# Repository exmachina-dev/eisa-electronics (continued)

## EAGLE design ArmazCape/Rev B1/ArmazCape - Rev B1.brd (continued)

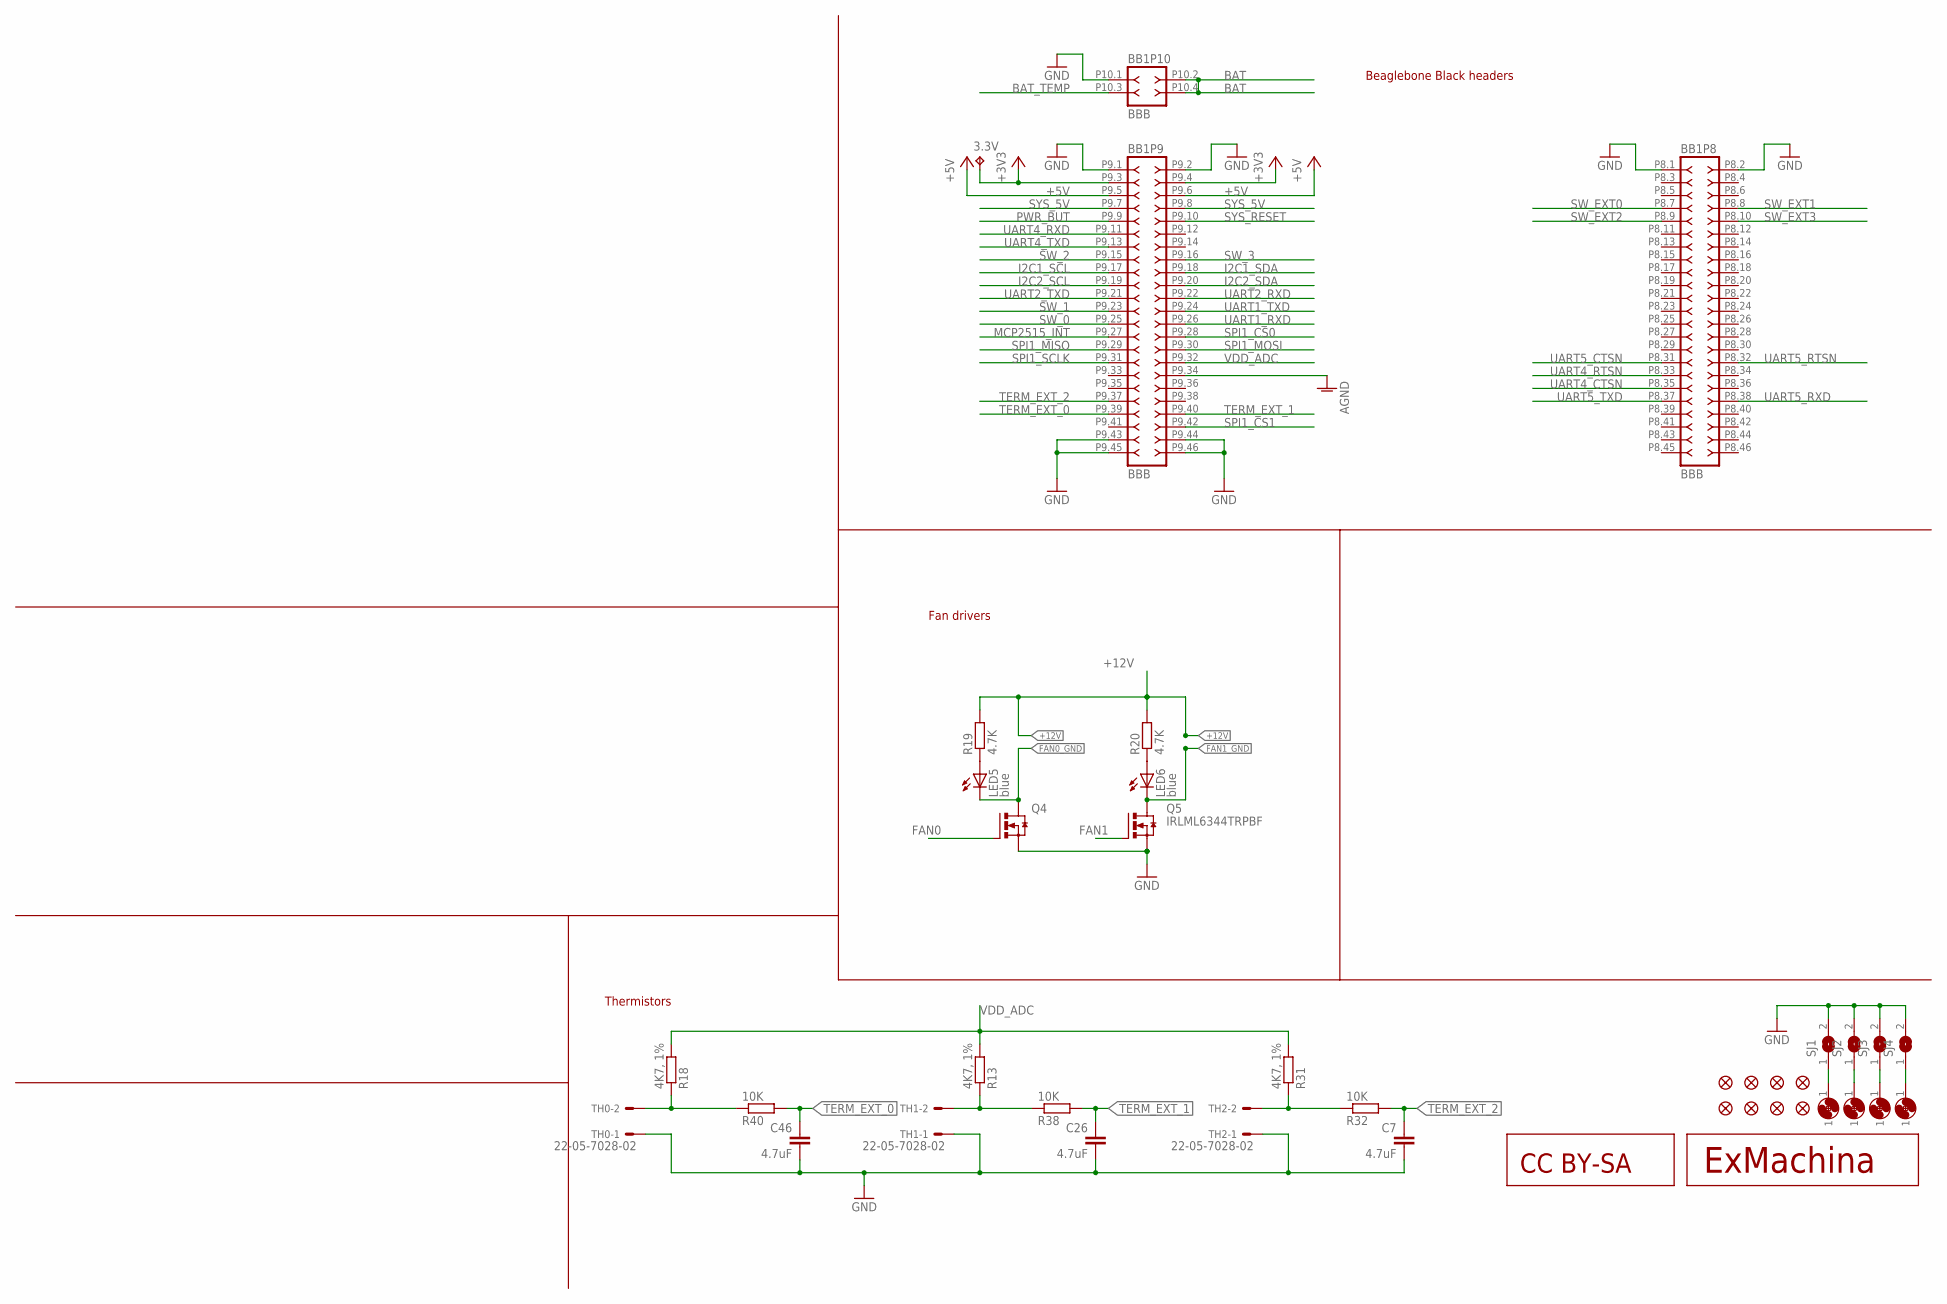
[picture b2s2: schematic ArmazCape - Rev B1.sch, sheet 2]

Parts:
3.3V: TPB1,27; B1,27
BB1: BBB
C7, C26, C46: 4.7uF; C0603; MPN MC0603X475K6R3CT
FI1, FI2, FI3, FI4, FI5, FI6, FI7, FI8: FIDUCIAL1X2; FIDUCIAL-1X2
H1, H2, H3, H4: MOUNT-PAD3,0; P3,0
LED5, LED6: blue; CHIP-LED0603; MPN OVS-0603
Q4, Q5: IRLML6344TRPBF; SOT95P240X112-3N
R13, R18, R31: 4K7, 1%; R0603; MPN MCMR06X4701FTL
R19, R20: 4.7K; R0603; MPN MCMR06X4701FTL
R32, R38, R40: 10K; R0603; MPN MCMR06X1002FTL
SJ1, SJ2, SJ3, SJ4: SJ
TH0, TH1, TH2: 22-05-7028-02; 7395-02; MPN 22-05-7028
U$1: EXMACHINA-LOGO-NAME; EXM-LOGO-BASELINE
U$2: CC-BY-SA

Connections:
+3V3: 3.3V.TP, BB1.P9.3 (3), BB1.P9.4 (4); also elsewhere on the board
+5V: BB1.P9.5 (5), BB1.P9.6 (6); also elsewhere on the board
+12V: R19.2, R20.2; also elsewhere on the board
AGND: BB1.P9.34 (34)
BAT: BB1.P10.2 (2), BB1.P10.4 (4); also elsewhere on the board
BAT_TEMP: BB1.P10.3 (3); also elsewhere on the board
FAN0: Q4.1 (G); also elsewhere on the board
FAN0_GND: LED5.C, Q4.3 (D); also elsewhere on the board
FAN1: Q5.1 (G); also elsewhere on the board
FAN1_GND: LED6.C, Q5.3 (D); also elsewhere on the board
GND: BB1.P8.1 (1), BB1.P8.2 (2), BB1.P9.1 (1), BB1.P9.2 (2), BB1.P9.43 (43), BB1.P9.44 (44), BB1.P9.45 (45), BB1.P9.46 (46), BB1.P10.1 (1), C7.2, C26.2, C46.2, Q4.2 (S), Q5.2 (S), SJ1.2, SJ2.2, SJ3.2, SJ4.2, TH0.1, TH1.1, TH2.1; also elsewhere on the board
I2C1_SCL: BB1.P9.17 (17)
I2C1_SDA: BB1.P9.18 (18)
I2C2_SCL: BB1.P9.19 (19); also elsewhere on the board
I2C2_SDA: BB1.P9.20 (20); also elsewhere on the board
MCP2515_INT: BB1.P9.27 (27); also elsewhere on the board
unnamed: LED5.A, R19.1
unnamed: R31.1, R32.1, TH2.2
unnamed: H4.1, SJ1.1
unnamed: H3.1, SJ2.1
unnamed: H2.1, SJ3.1
unnamed: H1.1, SJ4.1
unnamed: LED6.A, R20.1
unnamed: R13.1, R38.1, TH1.2
unnamed: R18.1, R40.1, TH0.2
PWR_BUT: BB1.P9.9 (9)
SPI1_CS0: BB1.P9.28 (28); also elsewhere on the board
SPI1_CS1: BB1.P9.42 (42)
SPI1_MISO: BB1.P9.29 (29); also elsewhere on the board
SPI1_MOSI: BB1.P9.30 (30); also elsewhere on the board
SPI1_SCLK: BB1.P9.31 (31); also elsewhere on the board
SW_0: BB1.P9.25 (25); also elsewhere on the board
SW_1: BB1.P9.23 (23); also elsewhere on the board
SW_2: BB1.P9.15 (15); also elsewhere on the board
SW_3: BB1.P9.16 (16); also elsewhere on the board
SW_EXT0: BB1.P8.7 (7); also elsewhere on the board
SW_EXT1: BB1.P8.8 (8); also elsewhere on the board
SW_EXT2: BB1.P8.9 (9); also elsewhere on the board
SW_EXT3: BB1.P8.10 (10); also elsewhere on the board
SYS_5V: BB1.P9.7 (7), BB1.P9.8 (8); also elsewhere on the board
SYS_RESET: BB1.P9.10 (10); also elsewhere on the board
TERM_EXT_0: BB1.P9.39 (39), C46.1, R40.2
TERM_EXT_1: BB1.P9.40 (40), C26.1, R38.2
TERM_EXT_2: BB1.P9.37 (37), C7.1, R32.2
UART1_RXD: BB1.P9.26 (26)
UART1_TXD: BB1.P9.24 (24)
UART2_RXD: BB1.P9.22 (22)
UART2_TXD: BB1.P9.21 (21)
UART4_CTSN: BB1.P8.35 (35)
UART4_RTSN: BB1.P8.33 (33)
UART4_RXD: BB1.P9.11 (11); also elsewhere on the board
UART4_TXD: BB1.P9.13 (13)
UART5_CTSN: BB1.P8.31 (31)
UART5_RTSN: BB1.P8.32 (32)
UART5_RXD: BB1.P8.38 (38); also elsewhere on the board
UART5_TXD: BB1.P8.37 (37); also elsewhere on the board
VDD_ADC: BB1.P9.32 (32), R13.2, R18.2, R31.2

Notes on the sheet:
Fan drivers
Thermistors
Beaglebone Black headers

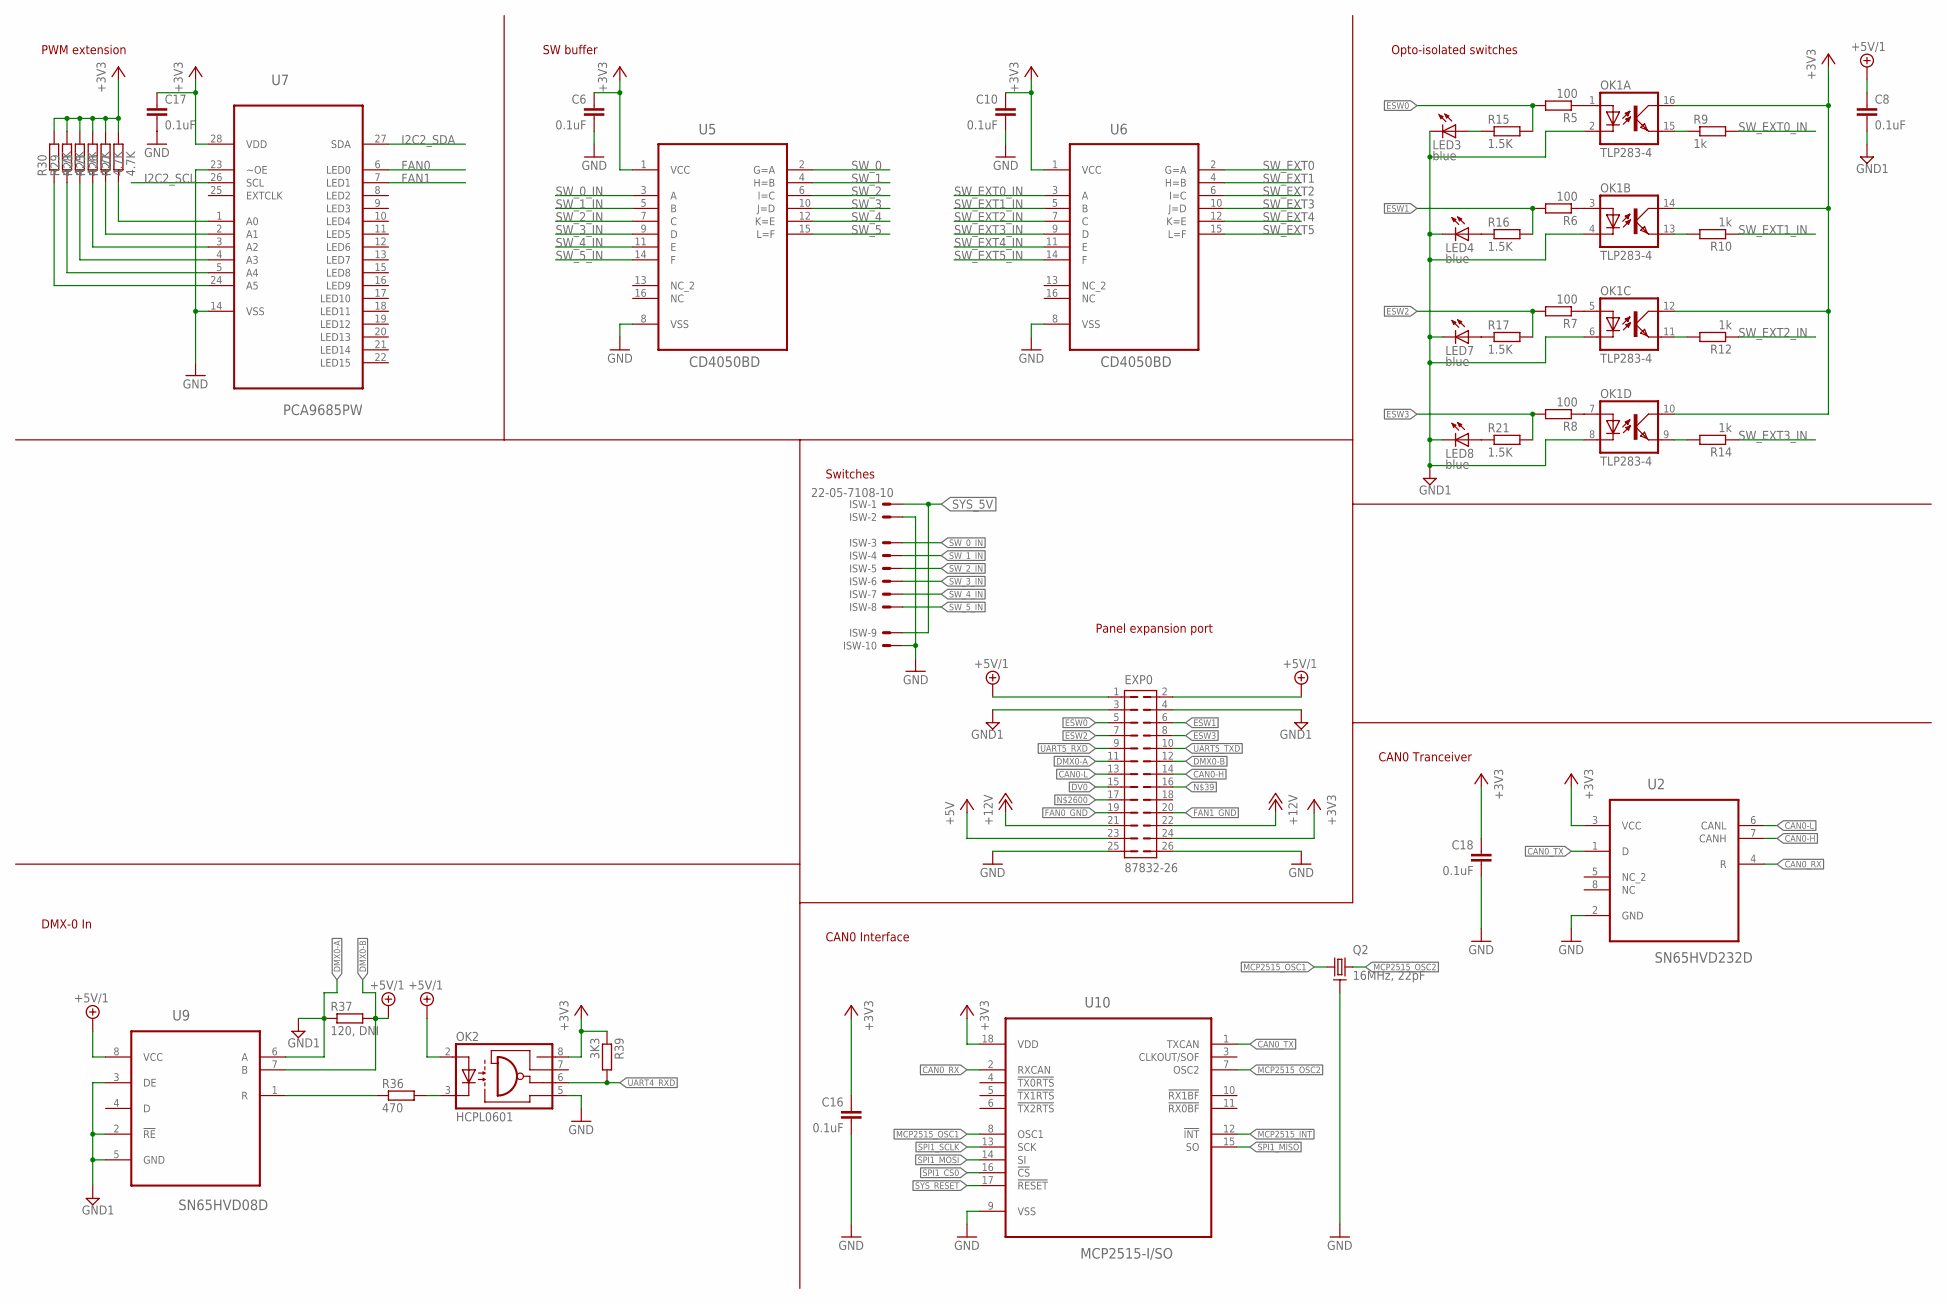
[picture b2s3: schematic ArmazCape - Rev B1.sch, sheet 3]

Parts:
C6, C8, C10, C16, C17, C18: 0.1uF; C0603; MPN MC0603B104K250CT
EXP0: 87832-26; MPN 87832-2620
ISW: 22-05-7108-10; 7395-10; MPN 22-05-7108
LED3, LED4, LED7, LED8: blue; CHIP-LED0603; MPN OVS-0603
OK1: TLP283-4; MINI-FLAT-16; MPN TCMT4100
OK2: HCPL0601; SOIC08
Q2: 16MHz, 22pF; AWSCR-MT; MPN AWSCR-16.00MTD-T
R5, R6, R7, R8: 100; R0603; MPN MCMR06X1000FTL
R9, R10, R12, R14: 1k; R0603; MPN MCMR06X1001FTL
R15, R16, R17, R21: 1.5K; R0603; MPN MCMR06X1501FTL
R25, R26, R27, R28, R29, R30: 4.7K; R0603; MPN MCMR06X4701FTL
R36: 470; R0603; MPN MCMR06X4700FTL
R37: 120, DNI; R0603; MPN MCMR06X1200FTL
R39: 3K3; R0603; MPN MCMR04X3301FTL
U2: SN65HVD232D; SOIC127P600X175-8N
U5, U6: CD4050BD; SOIC127P600X175-16N
U7: PCA9685PW; SOP65P640X110-28N
U9: SN65HVD08D; SOIC127P600X175-8N
U10: MCP2515-I/SO; SOIC127P1034X264-18N

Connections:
+3V3: C6.1, C10.1, C16.1, C17.1, C18.1, EXP0.24, OK1.10 (COL), OK1.12 (COL), OK1.14 (COL), OK1.16 (COL), OK2.8 (VCC), R25.2, R26.2, R27.2, R28.2, R29.2, R30.2, R39.1, U2.3 (VCC), U5.1 (VCC), U6.1 (VCC), U7.28 (VDD), U10.18 (VDD); also elsewhere on the board
+5V: EXP0.23; also elsewhere on the board
+5V/1: C8.1, EXP0.1, EXP0.2, OK2.2 (A), U9.8 (VCC); also elsewhere on the board
+12V: EXP0.21, EXP0.22; also elsewhere on the board
CAN0-H: EXP0.14, U2.7 (CANH)
CAN0-L: EXP0.13, U2.6 (CANL)
CAN0_RX: U2.4 (R), U10.2 (RXCAN)
CAN0_TX: U2.1 (D), U10.1 (TXCAN)
DMX0-A: EXP0.11, R37.1, U9.6 (A)
DMX0-B: EXP0.12, R37.2, U9.7 (B)
DV0: EXP0.15; also elsewhere on the board
ESW0: EXP0.5, R5.2, R15.2
ESW1: EXP0.6, R6.2, R16.2
ESW2: EXP0.7, R7.2, R17.2
ESW3: EXP0.8, R8.2, R21.2
FAN0: U7.6 (LED0); also elsewhere on the board
FAN0_GND: EXP0.19; also elsewhere on the board
FAN1: U7.7 (LED1); also elsewhere on the board
FAN1_GND: EXP0.20; also elsewhere on the board
GND: C6.2, C10.2, C16.2, C17.2, C18.2, EXP0.25, EXP0.26, ISW.2, ISW.10, OK2.5 (GND), Q2.2, U2.2 (GND), U5.8 (VSS), U6.8 (VSS), U7.14 (VSS), U7.23 (~OE), U10.9 (VSS); also elsewhere on the board
GND1: C8.2, EXP0.3, EXP0.4, LED3.C, LED4.C, LED7.C, LED8.C, OK1.2 (C), OK1.4 (C), OK1.6 (C), OK1.8 (C), U9.2 (!RE), U9.3 (DE), U9.5 (GND); also elsewhere on the board
I2C2_SCL: U7.26 (SCL); also elsewhere on the board
I2C2_SDA: U7.27 (SDA); also elsewhere on the board
MCP2515_INT: U10.12 (!INT); also elsewhere on the board
MCP2515_OSC1: Q2.1, U10.8 (OSC1)
MCP2515_OSC2: Q2.3, U10.7 (OSC2)
unnamed: OK1.1 (A), R5.1
unnamed: OK1.15 (EMIT), R9.1
unnamed: OK1.7 (A), R8.1
unnamed: OK1.9 (EMIT), R14.2
unnamed: OK1.11 (EMIT), R12.2
unnamed: OK1.13 (EMIT), R10.2
unnamed: LED3.A, R15.1
unnamed: OK1.3 (A), R6.1
unnamed: LED4.A, R16.1
unnamed: LED7.A, R17.1
unnamed: LED8.A, R21.1
unnamed: OK1.5 (A), R7.1
unnamed: R36.1, U9.1 (R)
unnamed: OK2.3 (C), R36.2
unnamed: R27.1, U7.1 (A0)
unnamed: R26.1, U7.2 (A1)
unnamed: R25.1, U7.3 (A2)
unnamed: R28.1, U7.4 (A3)
unnamed: R29.1, U7.5 (A4)
unnamed: R30.1, U7.24 (A5)
SPI1_CS0: U10.16 (!CS); also elsewhere on the board
SPI1_MISO: U10.15 (SO); also elsewhere on the board
SPI1_MOSI: U10.14 (SI); also elsewhere on the board
SPI1_SCLK: U10.13 (SCK); also elsewhere on the board
SW_0: U5.2 (G=A); also elsewhere on the board
SW_0_IN: ISW.3, U5.3 (A)
SW_1: U5.4 (H=B); also elsewhere on the board
SW_1_IN: ISW.4, U5.5 (B)
SW_2: U5.6 (I=C); also elsewhere on the board
SW_2_IN: ISW.5, U5.7 (C)
SW_3: U5.10 (J=D); also elsewhere on the board
SW_3_IN: ISW.6, U5.9 (D)
SW_4: U5.12 (K=E)
SW_4_IN: ISW.7, U5.11 (E)
SW_5: U5.15 (L=F)
SW_5_IN: ISW.8, U5.14 (F)
SW_EXT0: U6.2 (G=A); also elsewhere on the board
SW_EXT0_IN: R9.2, U6.3 (A)
SW_EXT1: U6.4 (H=B); also elsewhere on the board
SW_EXT1_IN: R10.1, U6.5 (B)
SW_EXT2: U6.6 (I=C); also elsewhere on the board
SW_EXT2_IN: R12.1, U6.7 (C)
SW_EXT3: U6.10 (J=D); also elsewhere on the board
SW_EXT3_IN: R14.1, U6.9 (D)
SW_EXT4: U6.12 (K=E)
SW_EXT4_IN: U6.11 (E)
SW_EXT5: U6.15 (L=F)
SW_EXT5_IN: U6.14 (F)
SYS_5V: ISW.1, ISW.9; also elsewhere on the board
SYS_RESET: U10.17 (!RESET); also elsewhere on the board
UART4_RXD: OK2.6 (VO), R39.2; also elsewhere on the board
UART5_RXD: EXP0.9; also elsewhere on the board
UART5_TXD: EXP0.10; also elsewhere on the board

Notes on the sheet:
Switches
PWM extension
SW buffer
Opto-isolated switches
Panel expansion port
DMX-0 In
CAN0 Interface
CAN0 Tranceiver

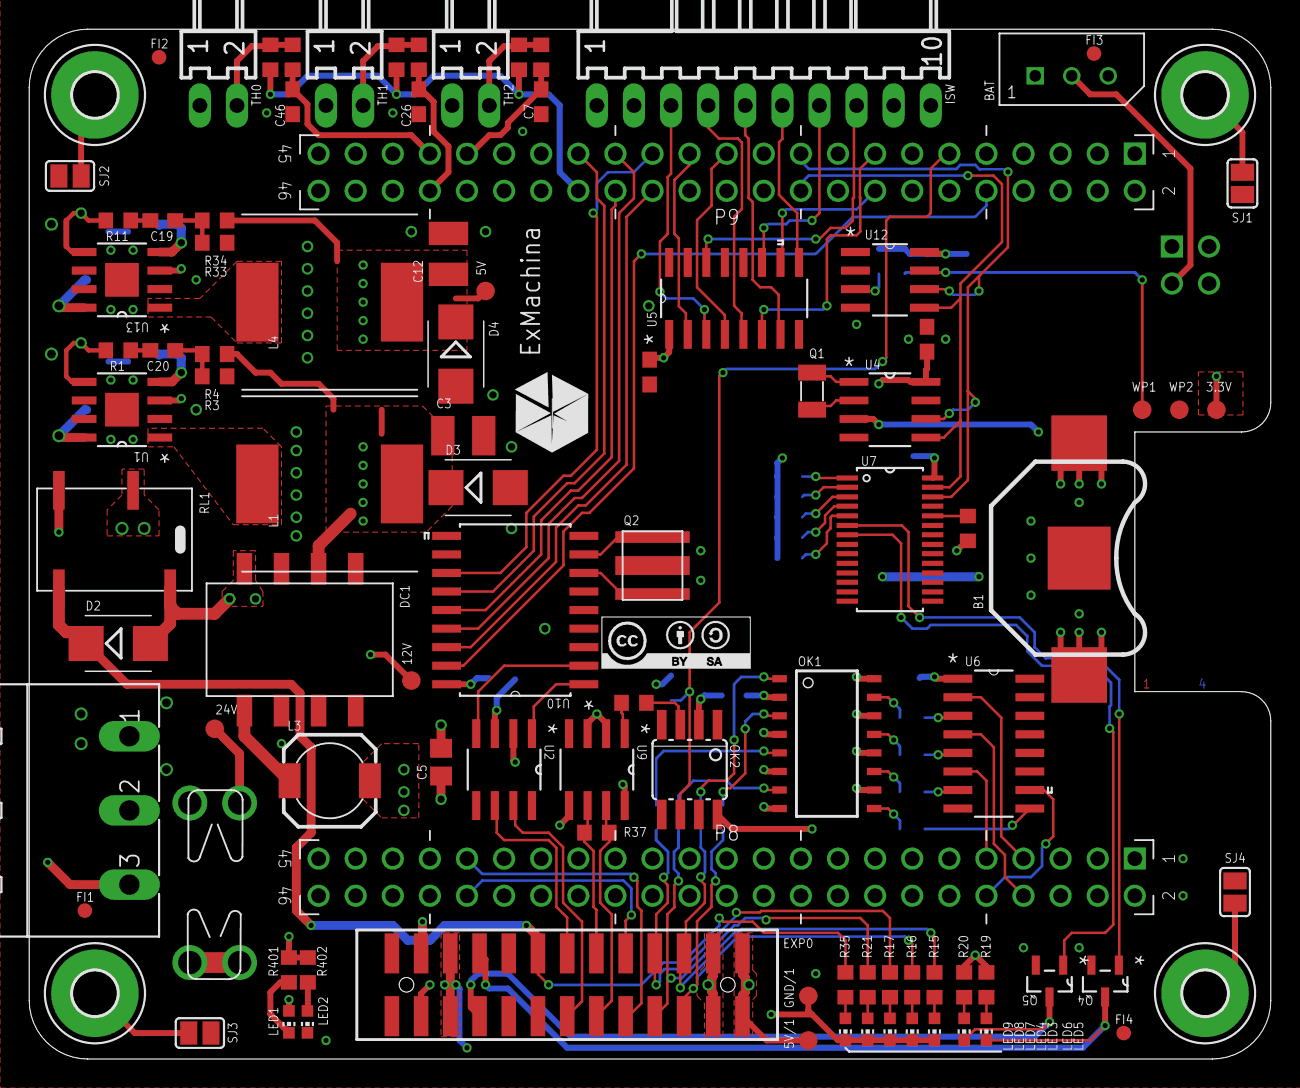
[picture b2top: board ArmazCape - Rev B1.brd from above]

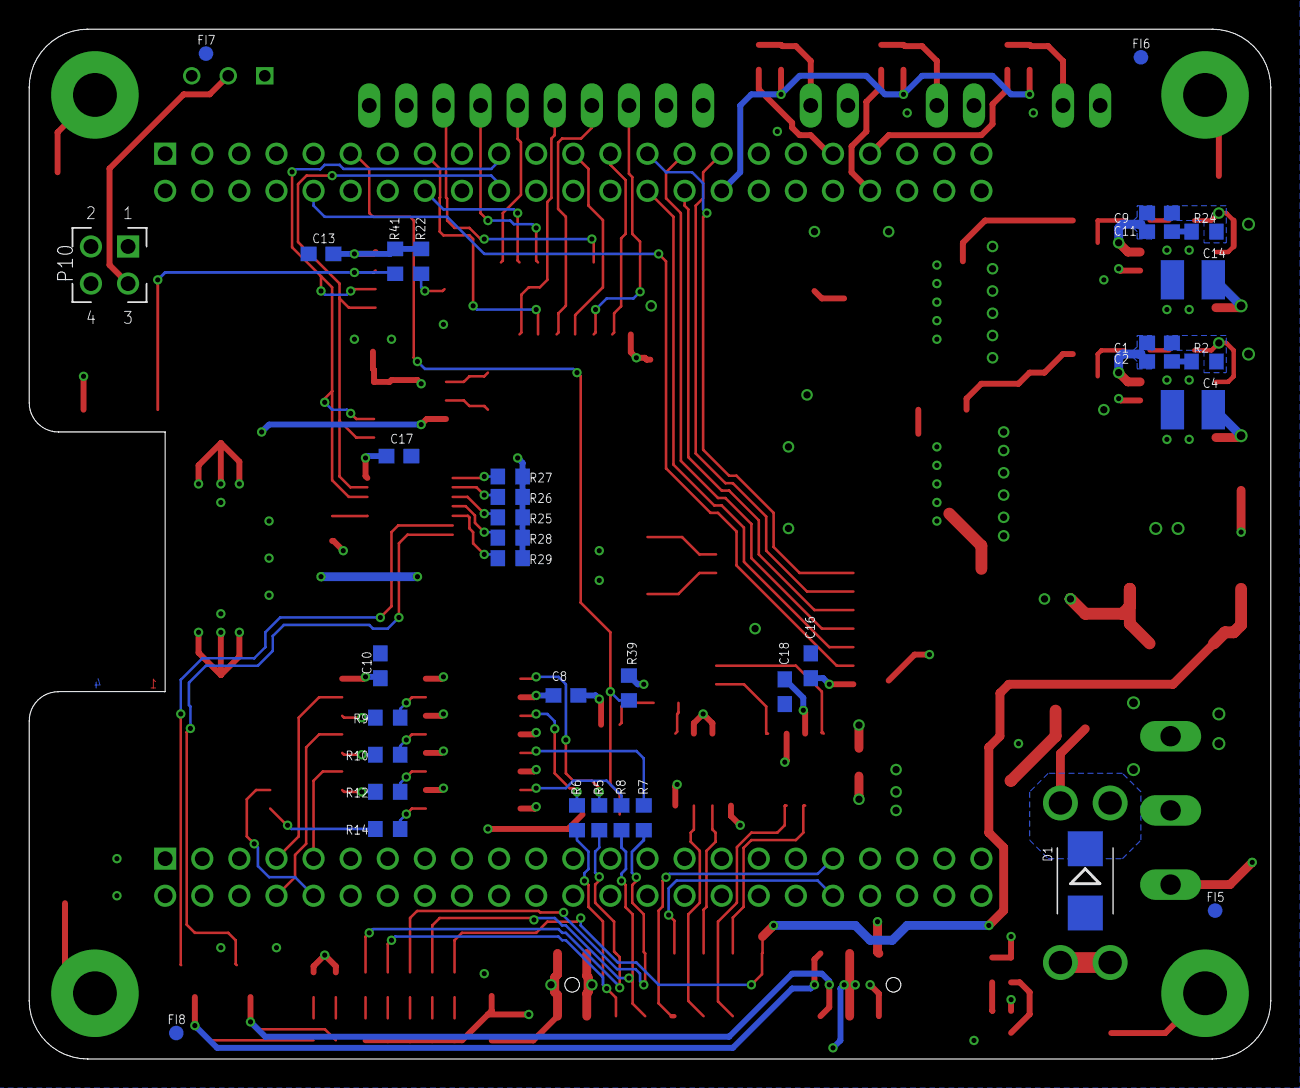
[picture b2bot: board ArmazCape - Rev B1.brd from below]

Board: 4 copper layers, 85.0 x 70.5 mm, 135 parts (35 on the bottom side), 112 nets.

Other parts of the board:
U$3: A4L-LOC

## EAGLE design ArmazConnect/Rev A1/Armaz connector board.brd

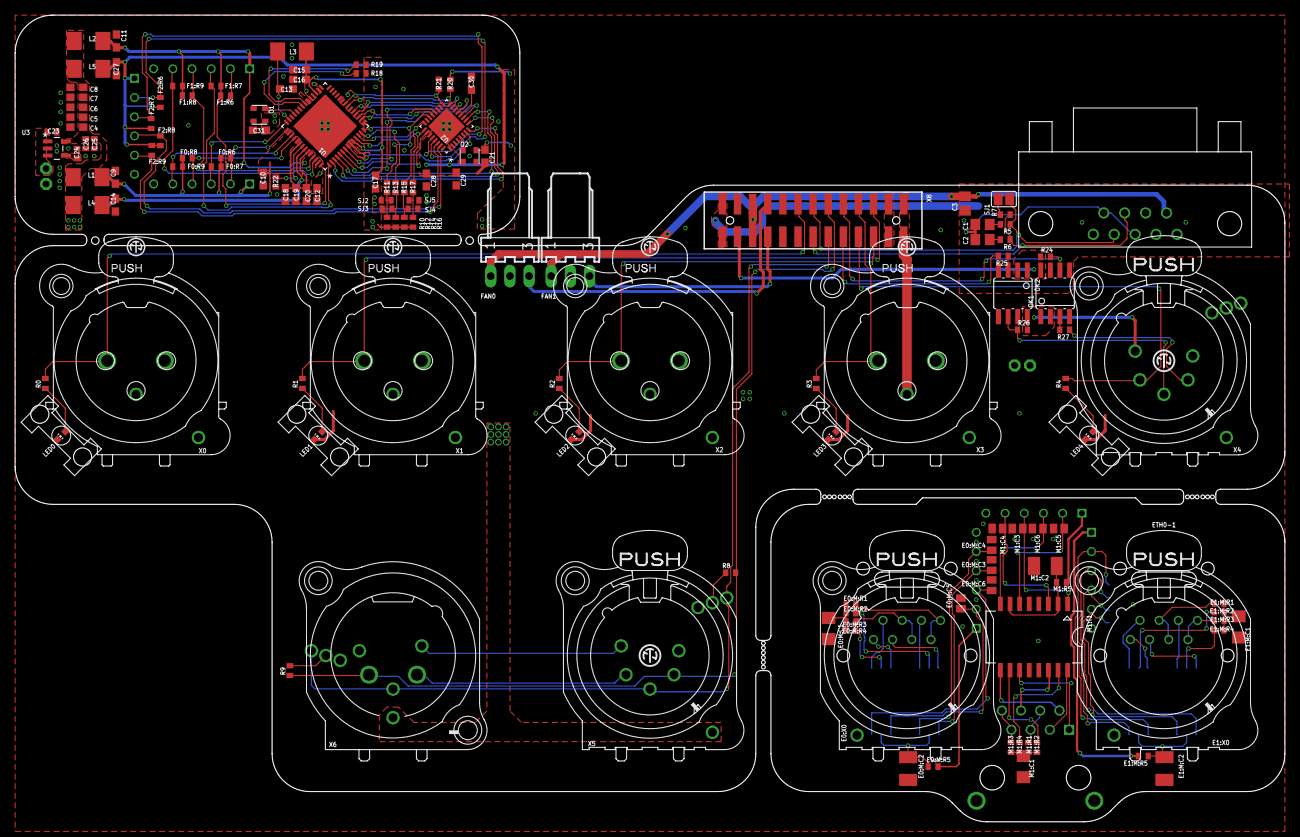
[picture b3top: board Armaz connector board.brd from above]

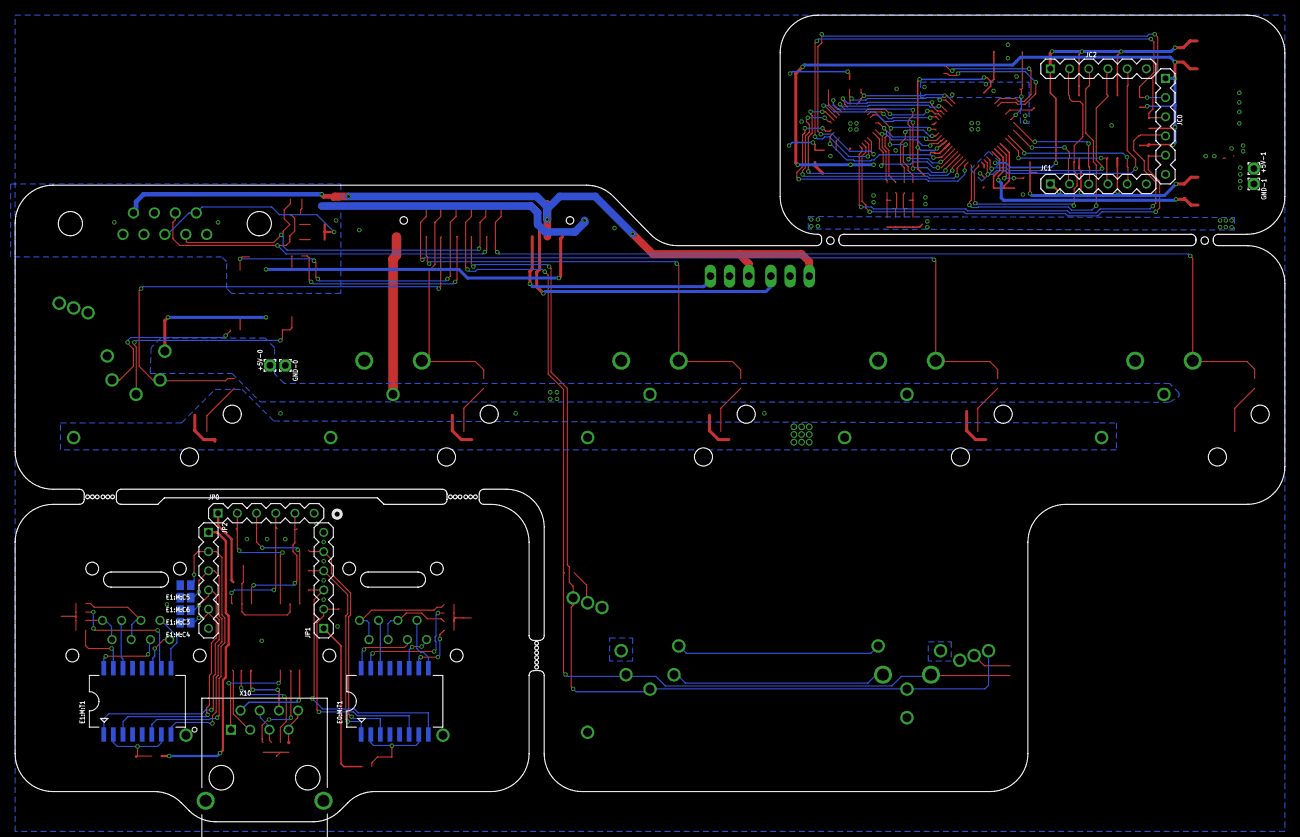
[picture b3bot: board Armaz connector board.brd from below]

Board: 2 copper layers, 168.0 x 106.7 mm, 156 parts (17 on the bottom side), 129 nets.

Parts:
+5V-0, +5V-1: WIREPAD1,6/0,9; 1,6/0,9
C1, C2: 560pF; C0805
C3: 1uF; C0805
C4, C9, C10, C11, C12, C13, C14, C15, C18: 4.7uF, 6.3V, 20%; C0603
C5, C6, C8, C16, C17, C19, C20: 0.1uF, 16V, 10%; C0603
C7: 0.1uF; C0603
C21, C31: 0.01uF, 6V, 10%; C0603
C23: 1uF, 16V; C0402
C24: 10nF, 50V; C0402
C25: 4.7uF, 6.3V; C0402
C26: 0.1uF, 16V; C0402
C27: 4.7uF, 6.3V; C0603
C28, C29, C30: 0.1uF, 16V; C0603
E0:M:C1, E1:M:C1: 1000pF, 2kV; C1206
E0:M:C2, E1:M:C2: .022uF; SMC_B
E0:M:C3, E0:M:C4, E0:M:C5, E0:M:C6, E1:M:C3, E1:M:C4, E1:M:C5, E1:M:C6: 15pF, 50V; C0504
E0:M:R1, E0:M:R2, E0:M:R3, E0:M:R4, E1:M:R1, E1:M:R2, E1:M:R3, E1:M:R4: 75; R0402
E0:M:R5, E1:M:R5: 10, 1/8W, 1%; R0402
E0:M:T1, E1:M:T1: 749010012
E0:X0, E1:X0: NE8FAV
F0:R6, F0:R7, F0:R8, F0:R9, F1:R6, F1:R7, F1:R8, F1:R9, F2:R6, F2:R7, F2:R8, F2:R9: 49.9, 1/8W, 1%; R0402
FAN0, FAN1: 22-05-7038-03; 7395-03
GND-0, GND-1: WIREPAD1,6/0,9; 1,6/0,9
JC0, JC1, JC2: 1X06
JP0, JP1, JP2: 1X06
L1, L2, L3, L4, L5: 2.0A/0.05 DCR; L4532M
LED0, LED1, LED2, LED3, LED4: blue; CHIP-LED0603
M1:C1: 1000pF, 2kV; C1206
M1:C2: .022uF; SMC_B
M1:C3, M1:C4, M1:C5, M1:C6: 15pF, 50V; C0504
M1:R1, M1:R2, M1:R3, M1:R4: 75; R0402
M1:R5: 10, 1/8W, 1%; R0402
M1:T1: 749010012
O1, O2: 25MHz; ADSM
OK1, OK2: HCPL0601; SOIC08
R0, R1, R2, R3, R4: 1.5K; R0402
R5, R6: 100; R0402
R7: 120; R0402
R8, R9: 120, 1/4W; R0402
R10, R11, R12, R13, R14, R15, R16, R17, R18, R19, R20, R21: 10K, 1/10W, 1%; R0402
R22: 12K4, 1%; R0402
R24: 3K3; R0402
R25: 330; R0402
R26, R27: 4K7; R0402
SJ1: SJ
SJ2, SJ3, SJ4, SJ5: O, DNI; R0402
U1: LAN9303-ABZJ; QFN50P800X800X100-57N
U2: LAN8710AI-EZK; QFN50P500X500X100-33N
U3: LP2992IM5-3.3; SOT95P284X122-5N
U$1, U$2, U$3, U$4, U$5: 1275.100
X0, X1, X2, X3: NC3FAAV2; NC3FAV2
X4, X5: NC5FAV-SW
X6: NC5MAV-SW
X7: 5504F1-09S-02A-03; 5504F1-09S-02A
X8: 87832-26
X10: 85505-5113; MOLEX_85505-5113

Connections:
+3V3: C4.1, C5.1, C6.1, C7.1, C8.1, C21.1, C25.1, C26.1, C31.1, L1.1, L2.1, L4.1, L5.1, O1.4, O2.4, R10.1, R12.1, R14.1, R16.1, R18.2, R19.2, R20.2, U1.9, U1.15, U1.23, U1.30, U1.32, U1.33, U3.5
+5V: +5V-0.1, +5V-1.1, C23.1, OK1.2, OK2.8, R26.2, U3.1, U3.3, X0.3, X1.3, X2.3, X3.3, X4.5, X8.1, X8.2
+12V: C3.1, FAN0.1, FAN1.1, X7.9, X8.21, X8.22
AVDD: C27.1, C28.1, C29.1, F2:R6.2, F2:R7.2, F2:R8.2, F2:R9.2, JC0.1, L5.2, U2.1, U2.27
CAN0-H: R6.2, R7.2, X7.7, X8.14
CAN0-L: R5.2, SJ1.1, X7.2, X8.13
CAN0_GND: C1.2, C2.2, X7.3, X7.6
DMX0-A: R8.1, R9.1, X5.2, X6.2, X8.11
DMX0-B: X5.3, X5.NO, X6.3, X6.NO, X8.12
DUPLEX_POL_0: R16.2, R17.1, SJ5.1
DV0: R0.2, X0.2, X8.15
E0:M:N$1: E0:M:C2.+, E0:M:R5.1, E0:M:T1.2, E0:M:T1.7
E0:M:N$2: E0:M:R2.1, E0:M:T1.10
E0:M:N$3: E0:M:R4.1, E0:M:T1.15
E0:M:N$8: E0:M:C1.1, E0:M:R1.1, E0:M:R2.2, E0:M:R3.1, E0:M:R4.2
E0:N$1: E0:M:T1.11, E0:X0.1
E0:N$2: E0:M:T1.9, E0:X0.2
E0:N$3: E0:M:T1.16, E0:X0.3
E0:N$4: E0:M:T1.14, E0:X0.6
E0:N$5: E0:M:R1.2, E0:X0.4, E0:X0.5
E0:N$6: E0:M:R3.2, E0:X0.7, E0:X0.8
E1:M:N$1: E1:M:C2.+, E1:M:R5.1, E1:M:T1.2, E1:M:T1.7
E1:M:N$2: E1:M:R2.1, E1:M:T1.10
E1:M:N$3: E1:M:R4.1, E1:M:T1.15
E1:M:N$8: E1:M:C1.1, E1:M:R1.1, E1:M:R2.2, E1:M:R3.1, E1:M:R4.2
E1:N$1: E1:M:T1.11, E1:X0.1
E1:N$2: E1:M:T1.9, E1:X0.2
E1:N$3: E1:M:T1.16, E1:X0.3
E1:N$4: E1:M:T1.14, E1:X0.6
E1:N$5: E1:M:R1.2, E1:X0.4, E1:X0.5
E1:N$6: E1:M:R3.2, E1:X0.7, E1:X0.8
EE_SCL/SCL: R18.1, U1.36
EE_SDA/SDA: R19.1, U1.35
ESW0: R1.2, X1.2, X8.5
ESW1: R2.2, X2.2, X8.6
ESW2: R3.2, X3.2, X8.7
ESW3: R4.2, X4.4, X8.8
ESW3-RX: R27.1, X4.2
ESW3-TX: OK2.6, R26.1, X4.3
FAN0_GND: FAN0.3, X8.19
FAN1_GND: FAN1.3, X8.20
GND: C4.2, C5.2, C6.2, C7.2, C8.2, C9.2, C10.2, C11.2, C12.2, C13.2, C14.2, C15.2, C16.2, C17.2, C18.2, C19.2, C20.2, C21.2, C23.2, C24.2, C25.2, C26.2, C27.2, C28.2, C29.2, C30.2, C31.2, E0:M:C1.2, E0:M:C2.-, E0:M:C3.2, E0:M:C4.2, E0:M:C5.2, E0:M:C6.2, E0:X0.G, E1:M:C1.2, E1:M:C2.-, E1:M:C3.2, E1:M:C4.2, E1:M:C5.2, E1:M:C6.2, E1:X0.G, GND-0.1, GND-1.1, JC0.6, JC1.6, JC2.6, JP0.6, JP1.6, JP2.6, LED0.C, LED1.C, LED2.C, LED3.C, LED4.C, M1:C1.2, M1:C2.-, M1:C3.2, M1:C4.2, M1:C5.2, M1:C6.2, O1.2, O2.2, OK2.5, R21.1, R22.1, SJ2.2, SJ3.2, SJ4.2, SJ5.2, U1.34, U1.57, U3.2, X0.1, X1.1, X2.1, X3.1, X4.1, X5.1, X6.1, X8.3, X8.4, X10.M1, X10.M2
GND1: C3.2, OK1.5, X8.25, X8.26
GNDIO: X0.G, X1.G, X2.G, X3.G, X4.G, X5.G, X6.G
M1:N$1: M1:C2.+, M1:R5.1, M1:T1.2, M1:T1.7
M1:N$2: M1:R2.1, M1:T1.10
M1:N$3: M1:R4.1, M1:T1.15
M1:N$8: M1:C1.1, M1:R1.1, M1:R2.2, M1:R3.1, M1:R4.2
MDC: R21.2, U1.22, U2.17
MDIO: R20.1, U1.21, U2.16
unnamed: LED1.A, R1.1
unnamed: LED2.A, R2.1
unnamed: LED3.A, R3.1
unnamed: LED4.A, R4.1
unnamed: C1.1, R5.1
unnamed: C2.1, R6.1
unnamed: R7.1, SJ1.2
unnamed: R8.2, X5.N
unnamed: M1:T1.11, X10.1
unnamed: M1:T1.9, X10.2
unnamed: M1:T1.16, X10.3
unnamed: M1:R1.2, X10.4, X10.5
unnamed: M1:R3.2, X10.7, X10.8
unnamed: M1:T1.14, X10.6
unnamed: R9.2, X6.N
unnamed: LED0.A, R0.1
unnamed: OK2.3, R25.1
unnamed: C24.1, U3.4
unnamed: OK1.3, R27.2
unnamed: R22.2, U1.49
unnamed: E0:M:C5.1, E0:M:T1.6, JP1.2
unnamed: E0:M:C6.1, E0:M:T1.8, JP1.3
unnamed: E0:M:C3.1, E0:M:T1.1, JP1.4
unnamed: E0:M:C4.1, E0:M:T1.3, JP1.5
unnamed: JP0.4, M1:C3.1, M1:T1.1
unnamed: X5.4, X6.4
unnamed: X5.5, X6.5
unnamed: E1:M:R5.2, JP2.1
unnamed: JP0.1, M1:R5.2
unnamed: JP0.3, M1:C6.1, M1:T1.8
unnamed: JP0.2, M1:C5.1, M1:T1.6
unnamed: JP0.5, M1:C4.1, M1:T1.3
unnamed: E0:M:R5.2, JP1.1
unnamed: E1:M:C5.1, E1:M:T1.6, JP2.2
unnamed: E1:M:C6.1, E1:M:T1.8, JP2.3
unnamed: E1:M:C3.1, E1:M:T1.1, JP2.4
unnamed: E1:M:C4.1, E1:M:T1.3, JP2.5
P0_COL: U1.18, U2.15
P0_CRS: U1.19, U2.14
P0_INCLK: U1.8, U2.7
P0_IND0: U1.5, U2.11
P0_IND1: U1.4, U2.10
P0_IND2: U1.3, U2.9
P0_IND3: U1.2, U2.8
P0_INDV: U1.6, U2.26
P0_INER: U1.7, U2.13
P0_MODE0: R10.2, R11.1, SJ2.1
P0_MODE2: R14.2, R15.1, SJ4.1
P0_OUTCLK: U1.17, U2.20
P0_OUTD0/P0_MODE0: R11.2, U1.14, U2.22
P0_OUTD1/P0_MODE1: R13.2, U1.13
P0_OUTD2/P0_MODE2: R15.2, U1.12, U2.24
P0_OUTD3/DUPLEX_POL_0: R17.2, U1.11, U2.25
P0_OUTDV: U1.16, U2.21
PO_MODE1: R12.2, R13.1, SJ3.1
RXN0: F2:R9.1, JC0.5, U2.30
RXN1: F0:R9.1, JC1.5, U1.45
RXN2: F1:R9.1, JC2.5, U1.54
RXP0: F2:R8.1, JC0.4, U2.31
RXP1: F0:R8.1, JC1.4, U1.46
RXP2: F1:R8.1, JC2.4, U1.53
TXN0: F2:R7.1, JC0.3, U2.28
TXN1: F0:R7.1, JC1.3, U1.42
TXN2: F1:R7.1, JC2.3, U1.1
TXP0: F2:R6.1, JC0.2, U2.29
TXP1: F0:R6.1, JC1.2, U1.43
TXP2: F1:R6.1, JC2.2, U1.56
UART5_RXD: OK1.6, R24.2, X8.9
UART5_TXD: R25.2, X8.10
VDD18CORE: C15.1, C16.1, C17.1, L3.1, U1.10, U1.31
VDD18PLL: C13.1, L3.2, U1.41
VDD18TX: C18.1, C19.1, C20.1, U1.48, U1.51
VDD33A1: C9.1, C10.1, F0:R6.2, F0:R7.2, F0:R8.2, F0:R9.2, JC1.1, L1.2, U1.44, U1.47
VDD33A2: C11.1, C12.1, F1:R6.2, F1:R7.2, F1:R8.2, F1:R9.2, JC2.1, L2.2, U1.52, U1.55
VDD33BIAS: C14.1, L4.2, U1.50
VDDIO: C30.1, U2.12
VDD_3V3: OK1.8, OK2.2, R24.1, X8.24
XI: O1.3, U1.39
XTAL1/CLKIN: O2.3, U2.5
